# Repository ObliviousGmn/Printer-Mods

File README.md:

# Printer-Mods
Various of Printer Mods I've made

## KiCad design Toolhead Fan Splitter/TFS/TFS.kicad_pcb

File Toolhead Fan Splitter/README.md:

## -+- Toolhead Fan Splitter

Honestly Extremely Beta and Untested. Designed it for Mantis Xol.

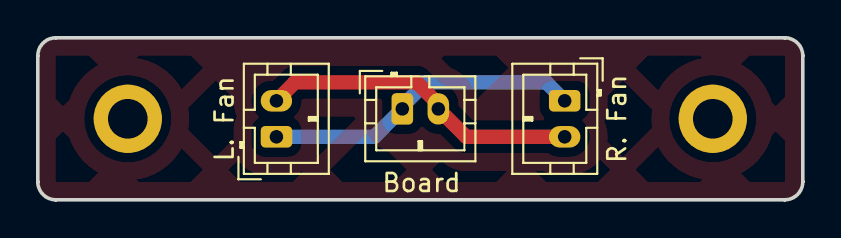
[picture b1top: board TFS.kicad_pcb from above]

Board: 2 copper layers, 42.5 x 9.0 mm, 3 parts (0 on the bottom side), 2 nets.

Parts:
Board: Board; JST_PH_B2B-PH-K_1x02_P2.00mm_Vertical
L. Fan: FAN1; JST_PH_B2B-PH-K_1x02_P2.00mm_Vertical
R. Fan: FAN2; JST_PH_B2B-PH-K_1x02_P2.00mm_Vertical

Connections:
GND: Board.2, L. Fan.2, R. Fan.2
VCC: Board.1, L. Fan.1, R. Fan.1

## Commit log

2023-03-24 Beta Release
2023-04-01 Create LICENSE
2023-04-10 Ptfe Arm Push
2023-04-11 Alpha
2023-04-27 no good
2023-05-25 User Photos
2023-06-13 Experimental Uploads
2023-06-13 Fixes
2023-06-15 Refresh
2023-09-25 New Content
2023-10-01 Revision 3
2024-01-13 Nyloc push
2025-04-17 Update
    Added PCB_Klicky Carriage
2025-04-17 Uploading STLs
